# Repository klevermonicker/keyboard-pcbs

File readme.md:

Amoeba Streamlined:

I enjoy the flexibility that we have with the Amoeba, but I feel it's just too flexible. Our goal is to make this a much more "streamlined" experience and friendlier to folks. Originals all live in the archive.

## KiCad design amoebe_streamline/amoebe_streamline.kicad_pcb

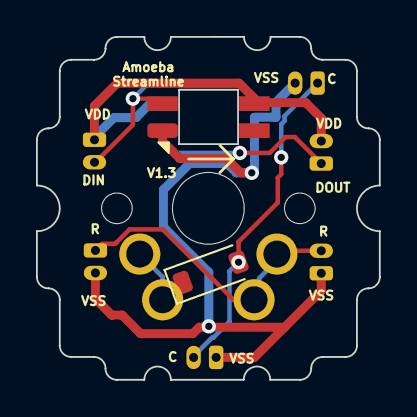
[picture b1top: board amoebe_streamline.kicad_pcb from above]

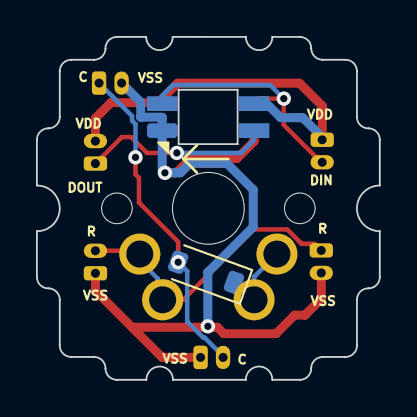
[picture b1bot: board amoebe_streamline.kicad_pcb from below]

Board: 2 copper layers, 19.1 x 19.1 mm, 11 parts (2 on the bottom side), 7 nets.

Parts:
D1, D1#2: 1N4148W-7-F; D_SOD-123
D2, D2#2: SK6812MINI_E; SK6812-MINI-E
J1, J2, J3, J4, J5, J6: Conn_01x02_Pin; Molex_PicoBlade_53047-0210_1x02_P1.25mm_Vertical
S1: MX1A; SW_MX_reversible

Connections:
/C: D1.2 (K), D1#2.2 (K), J5.2, J6.1
/DIN: D2.4 (DIN), D2#2.4 (DIN), J1.2
/DOUT: D2.2 (DOUT), D2#2.2 (DOUT), J3.1
/R: J2.2, J4.1, S1.1
/VDD: D2.1 (VDD), D2#2.1 (VDD), J1.1, J3.2
/VSS: D2.3 (VSS), D2#2.3 (VSS), J2.1, J4.2, J5.1, J6.2
unnamed: D1.1 (A), D1#2.1 (A), S1.2

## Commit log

2023-06-04 Initial
2023-06-04 Clean up
2023-12-14 what is wrong with me
2023-12-15 Finished schematic and routed traces
2023-12-15 Fixes data lines for LED
2023-12-15 Added 3d files
2023-12-15 version 1.2 with additional ground pins
2023-12-15 added gerber files
2023-12-15 added better gerber files
2024-03-08 updated pcb design to 1.3
2024-03-08 updated pcb design
